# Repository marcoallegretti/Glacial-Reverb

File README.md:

# Koloured-Verb

A 12 HP Eurorack stereo reverb built on a Daisy Patch SM, using the
[eurorack-blocks](https://github.com/ohmtech-rdi/eurorack-blocks) framework.
Three boards: a carrier for the Daisy, a control board, and the panel.

Twelve reverb voices grouped into six families, ten post-reverb tail effects
grouped into five families, and a freeze pad with ducking.

## Rooms

Selected with the **ROOM** button. Short press cycles the family (RGB colour),
long press cycles the variant within it (RGB brightness dips = variant number).

| Family  | Colour  | Variants                          |
|---------|---------|-----------------------------------|
| Hall    | blue    | FDN tank · chamber                |
| Plate   | green   | Dattorro · vintage · dispersive   |
| Spring  | cyan    | classic · long tank · dispersive  |
| Shimmer | yellow  | octave up · octave down (Abyss)   |
| Cloud   | magenta | granular over an FDN tank         |
| Ambient | red     | modulated Hadamard FDN            |

Three variants per family is the ceiling: the LED renders a variant as a shade
of the family colour, and a fourth step is not readable against off.

The chamber runs a Moorer early-reflection tap bank and feeds the tank from the
taps rather than from the input, so each tap seeds the tank and the density
builds without the reflections reading as discrete echoes. The vintage plate
holds its high-frequency decay near a second whatever the decay knob does, as a
steel plate does. The long tank spreads its three spring delays while keeping
their chirp cutoffs together — the inverse of the short tank — and scatters at
the mid-point coupling ring. The dispersive voices use stretched-allpass chains
for the chirp.

## Tail effects

Selected with the **FX** button, same gesture (short = family, long = variant).
The red LED blinks the family number; None leaves the LED off. Each effect is
added over the untouched tail, so amount 0 is a true bypass.

| Family   | Variants                       |
|----------|--------------------------------|
| None     | —                              |
| Pitch    | octave up · sub · chord (5th)  |
| Modulate | chorus · formant               |
| Texture  | granular · reverse             |
| Resonant | resonator · droplet            |

## Panel

| Control   | Function                                                        |
|-----------|-----------------------------------------------------------------|
| FX pot    | Morph: model character and tail-effect depth together           |
| DECAY     | Tail length                                                     |
| MIX       | Wet added over the dry (additive, not a crossfade)              |
| PRE DL    | Pre-delay                                                       |
| DUCK      | Input ducks the reverb                                          |
| FRZ LV    | Frozen pad level                                                |
| FRZ MX    | How much new signal enters the frozen pad                       |
| FRZ btn   | Short press = freeze on/off · long press = tank-only on/off     |
| ROOM btn  | Short = room family · long = variant                            |
| FX btn    | Short = effect family · long = variant                          |
| FRZ G     | Gate: forces freeze on                                          |
| FX / FRZ LV / MIX / DECAY | CV over the corresponding pot                   |
| IN L/R    | Audio in (R normalled to L)                                     |
| OUT L/R   | Audio out                                                       |

CV drives continuous character; the buttons handle discrete structure. Room and
effect selection step discretely rather than sweeping: a switch renders both
voices through a 150 ms crossfade and clears the outgoing one only once it is
silent, so the tail carries across a switch.

## Layout

```
eurorack/
  KoloredVerb.erbui          panel and control definition
  KoloredVerb.{h,cpp}        UI glue: selectors, gestures, LEDs
  KoloredVerbDsp.{h,cpp}     freeze pad, duck, mix, pre-delay wrapper
  dsp/                       reverb models, tail effects, shared DSP

hardware/
  core-board/                carrier: Daisy Patch SM, power, I/O expansion
  control-board/             pots, jacks, buttons, LEDs
  panel-board/               12 HP front panel
```

Each board folder holds its KiCad sources and a `fab/` directory with the
gerber zip and loose gerber set. See [hardware/README.md](hardware/README.md)
for the stack and what mates to what.

## Building

See [BUILD.md](BUILD.md) for the toolchain, firmware, simulator and board
fabrication. The `eurorack-blocks` framework is not vendored in this repository.

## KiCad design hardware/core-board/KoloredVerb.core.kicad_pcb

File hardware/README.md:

# Koloured-Verb — hardware

Three boards, one 12 HP module.

```
  panel-board      12 HP FR4 panel: cutouts and baked labels
       │  pots / jacks / LEDs poke through
  control-board    panel parts on F.Cu, carrier headers on B.Cu
       │  ZZ1-5 / ZZ7 / ZZ12 + J6 / J9 / J11 plug down into…
  core-board       Daisy Patch SM host, power, I/O expansion
       │  4× 5×2 sockets host…
  Daisy Patch SM   Electrosmith submodule (bought, not fabricated)
```

| Folder | Board | Size | Assembly |
|---|---|---|---|
| [`core-board/`](core-board/) | carrier | 59.75 × 109.65 mm | 45 SMD by JLCPCB, 12 through-hole by hand |
| [`control-board/`](control-board/) | pots, jacks, buttons, LEDs | 59.75 × 109.65 mm | all by hand; one SMD RGB LED |
| [`panel-board/`](panel-board/) | 12 HP panel | 60.75 × 128.65 mm | none |

All three are 2-layer, 1.6 mm FR4. Each folder holds its KiCad sources, a
`<board>.bom.csv`, and `fab/` with the gerber zip and the loose set it was built
from. The core board also carries `fab/*-jlcpcb-bom.csv` and `-cpl.csv` for
assembly.

`ZZ10` on the control board is **DNP** — the core board carries no microSD, so
that header has no mating socket.

## Gerbers

```sh
kicad-cli pcb export gerbers --no-protel-ext \
  --layers F.Cu,B.Cu,F.Mask,B.Mask,F.Paste,B.Paste,F.Silkscreen,B.Silkscreen,Edge.Cuts \
  -o <board>/fab/gerber/ <board>/<name>.kicad_pcb
kicad-cli pcb export drill -o <board>/fab/gerber/ <board>/<name>.kicad_pcb
```

then zipped from `fab/gerber/`. The panel yields no paste layers — it carries no
SMD pads.

## Regenerating

The panel comes from `eurorack/KoloredVerb.erbui`; its labels are baked vector
outlines and cannot be edited in KiCad:

```sh
python3 hardware/panel-board/regen_panel.py
```

The control board cannot be regenerated — `erbb build hardware` parses it with a
KiCad-6-era reader that throws on KiCad 10 net syntax. Edit it in KiCad and treat
the committed board as the source of truth.

The core board's assembly files are derived from its own PCB:

```sh
"…/KiCad/10.0/bin/python.exe" hardware/core-board/derive_assembly.py
```

## Licensing

The control board and panel are generated from eurorack-blocks blocks, and the
core board derives from its kivu12. All carry **CC BY-SA 4.0** by derivation.
See [THIRD-PARTY.md](../THIRD-PARTY.md).

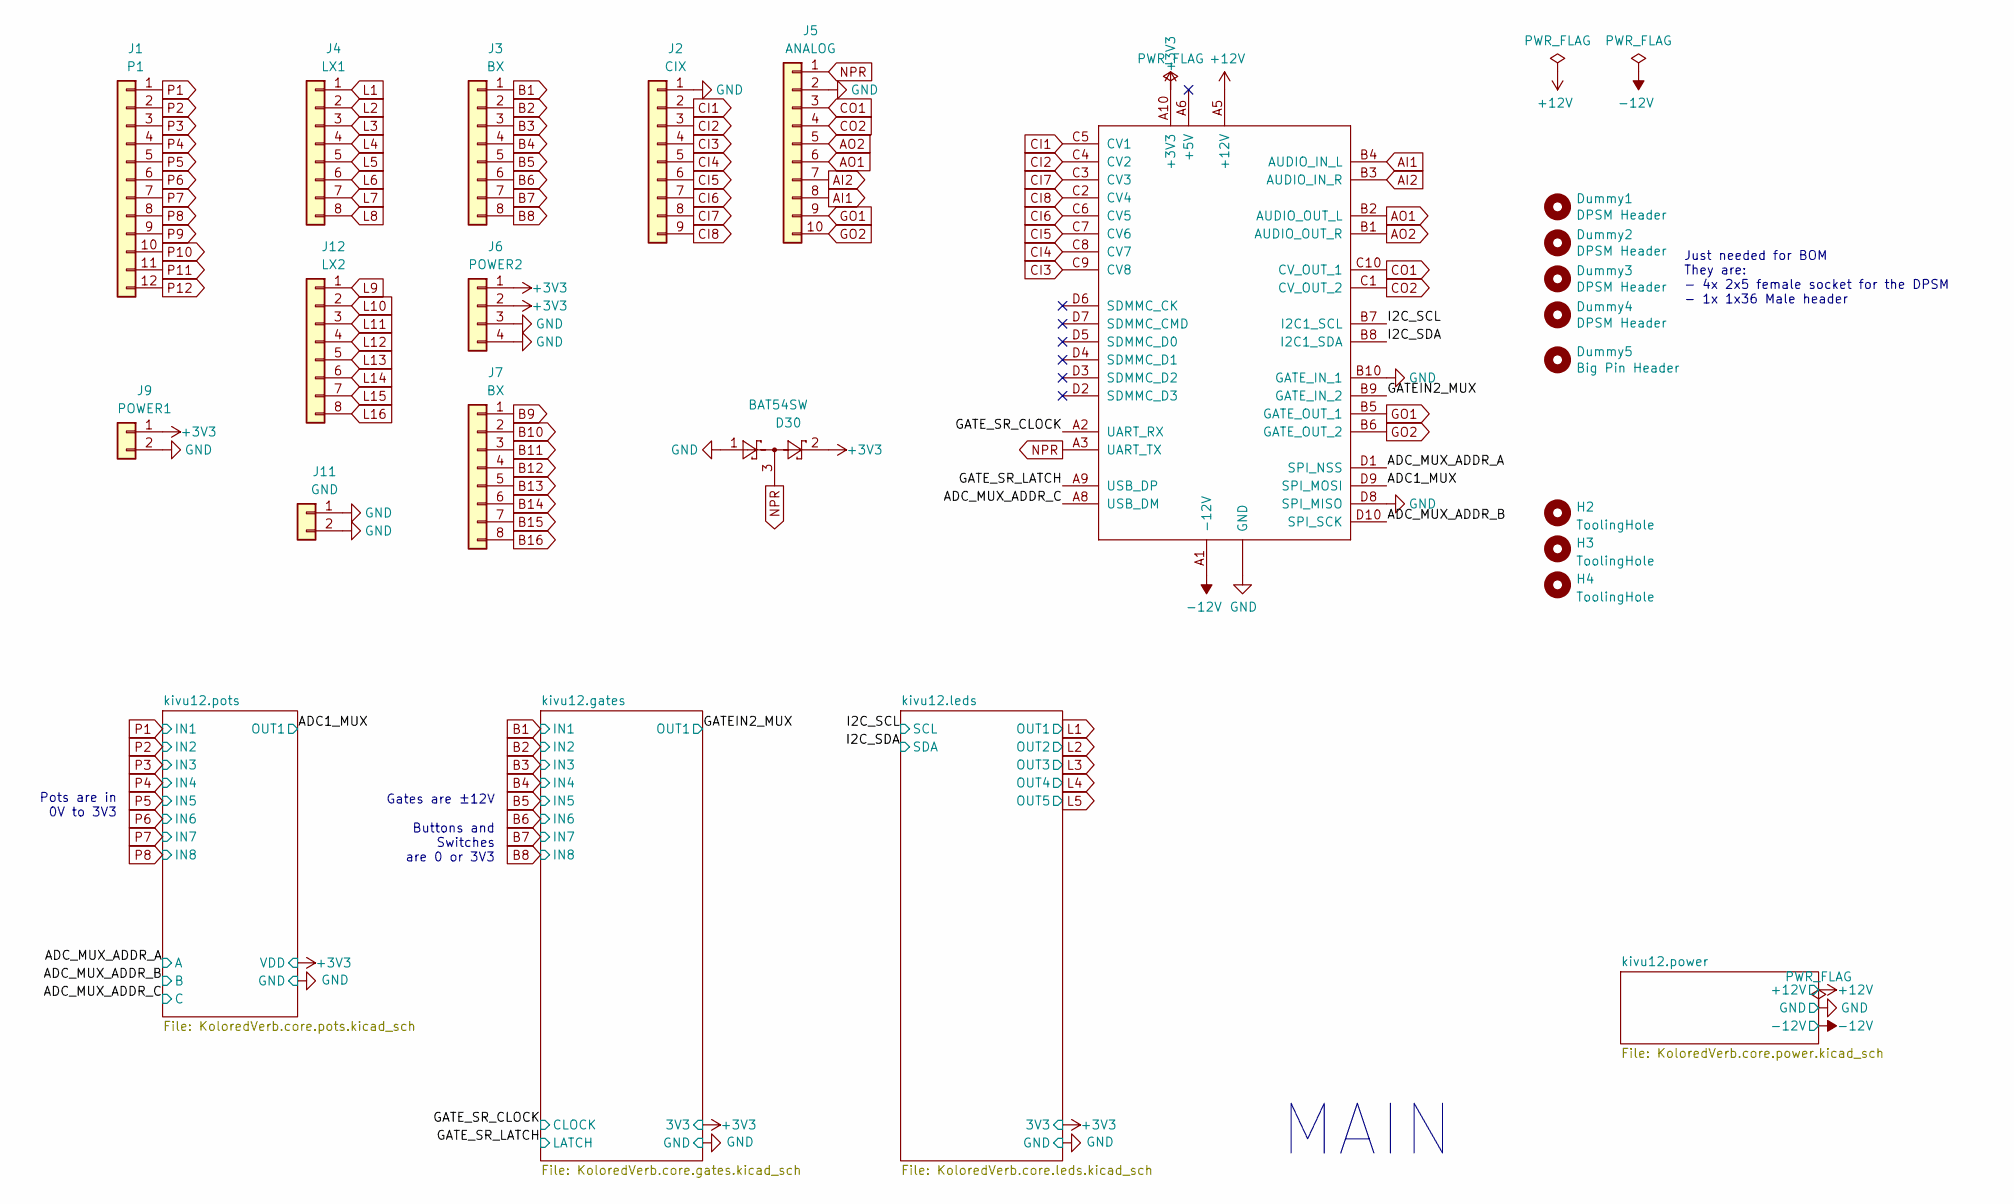
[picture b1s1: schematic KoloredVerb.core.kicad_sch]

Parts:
D30: BAT54SW; SOT-323_SC-70; MPN BAT54SW; JlcPcbPartNumber C22466373
DPSM1: DaisyPatchSm_Rev1; DaisyPatchSm; MPN DAISY-PATCH-SM
Dummy1, Dummy2, Dummy3, Dummy4: DPSM Header; Empty; MPN PPPC052LFBN-RC
Dummy5: Big Pin Header; Empty; MPN PBC36SAAN
H2, H3, H4: ToolingHole; JlcPcbToolingHole
J1: P1; PinSocket_1x12_P2.54mm_Vertical; MPN PPTC121LFBN-RC
J2: CIX; PinSocket_1x09_P2.54mm_Vertical; MPN PPTC091LFBN-RC
J3, J7: BX; PinSocket_1x08_P2.54mm_Vertical; MPN PPTC081LFBN-RC
J4: LX1; PinSocket_1x08_P2.54mm_Vertical; MPN PPTC081LFBN-RC
J5: ANALOG; PinSocket_1x10_P2.54mm_Vertical; MPN PPTC101LFBN-RC
J6: POWER2; PinSocket_1x04_P2.54mm_Vertical; MPN PPTC041LFBN-RC
J9: POWER1; PinSocket_1x02_P2.54mm_Vertical; MPN PPTC021LFBN-RC
J11: GND; PinSocket_1x02_P2.54mm_Vertical; MPN PPTC021LFBN-RC
J12: LX2; PinSocket_1x08_P2.54mm_Vertical; MPN PPTC081LFBN-RC

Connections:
+3V3: D30.2, DPSM1.A10 (+3V3), J6.1, J6.2, J9.1; also elsewhere on the board
+12V: DPSM1.A5 (+12V); also elsewhere on the board
-12V: DPSM1.A1 (-12V); also elsewhere on the board
/ADC1_MUX: DPSM1.D9 (SPI_MOSI); also elsewhere on the board
/ADC_MUX_ADDR_A: DPSM1.D1 (SPI_NSS); also elsewhere on the board
/ADC_MUX_ADDR_B: DPSM1.D10 (SPI_SCK); also elsewhere on the board
/ADC_MUX_ADDR_C: DPSM1.A8 (USB_DM); also elsewhere on the board
/GATEIN2_MUX: DPSM1.B9 (GATE_IN_2); also elsewhere on the board
/GATE_SR_CLOCK: DPSM1.A2 (UART_RX); also elsewhere on the board
/GATE_SR_LATCH: DPSM1.A9 (USB_DP); also elsewhere on the board
/I2C_SCL: DPSM1.B7 (I2C1_SCL); also elsewhere on the board
/I2C_SDA: DPSM1.B8 (I2C1_SDA); also elsewhere on the board
AI1: DPSM1.B4 (AUDIO_IN_L), J5.8
AI2: DPSM1.B3 (AUDIO_IN_R), J5.7
AO1: DPSM1.B2 (AUDIO_OUT_L), J5.6
AO2: DPSM1.B1 (AUDIO_OUT_R), J5.5
B1: J3.1; also elsewhere on the board
B2: J3.2; also elsewhere on the board
B3: J3.3; also elsewhere on the board
B4: J3.4; also elsewhere on the board
B5: J3.5; also elsewhere on the board
B6: J3.6; also elsewhere on the board
B7: J3.7; also elsewhere on the board
B8: J3.8; also elsewhere on the board
B9: J7.1
B10: J7.2
B11: J7.3
B12: J7.4
B13: J7.5
B14: J7.6
B15: J7.7
B16: J7.8
CI1: DPSM1.C5 (CV1), J2.2
CI2: DPSM1.C4 (CV2), J2.3
CI3: DPSM1.C9 (CV8), J2.4
CI4: DPSM1.C8 (CV7), J2.5
CI5: DPSM1.C7 (CV6), J2.6
CI6: DPSM1.C6 (CV5), J2.7
CI7: DPSM1.C3 (CV3), J2.8
CI8: DPSM1.C2 (CV4), J2.9
CO1: DPSM1.C10 (CV_OUT_1), J5.3
CO2: DPSM1.C1 (CV_OUT_2), J5.4
GND: D30.1, DPSM1.A4 (GND), DPSM1.A7 (GND), DPSM1.B10 (GATE_IN_1), DPSM1.D8 (SPI_MISO), J2.1, J5.2, J6.3, J6.4, J9.2, J11.1, J11.2; also elsewhere on the board
GO1: DPSM1.B5 (GATE_OUT_1), J5.9
GO2: DPSM1.B6 (GATE_OUT_2), J5.10
L1: J4.1; also elsewhere on the board
L2: J4.2; also elsewhere on the board
L3: J4.3; also elsewhere on the board
L4: J4.4; also elsewhere on the board
L5: J4.5; also elsewhere on the board
L6: J4.6
L7: J4.7
L8: J4.8
L9: J12.1
L10: J12.2
L11: J12.3
L12: J12.4
L13: J12.5
L14: J12.6
L15: J12.7
L16: J12.8
NPR: D30.3, DPSM1.A3 (UART_TX), J5.1
P1: J1.1; also elsewhere on the board
P2: J1.2; also elsewhere on the board
P3: J1.3; also elsewhere on the board
P4: J1.4; also elsewhere on the board
P5: J1.5; also elsewhere on the board
P6: J1.6; also elsewhere on the board
P7: J1.7; also elsewhere on the board
P8: J1.8; also elsewhere on the board
P9: J1.9
P10: J1.10
P11: J1.11
P12: J1.12

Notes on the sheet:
Just needed for BOM They are: - 4x 2x5 female socket for the DPSM - 1x 1x36 Male header
Pots are in 0V to 3V3
Gates are ±12V Buttons and Switches are 0 or 3V3
MAIN

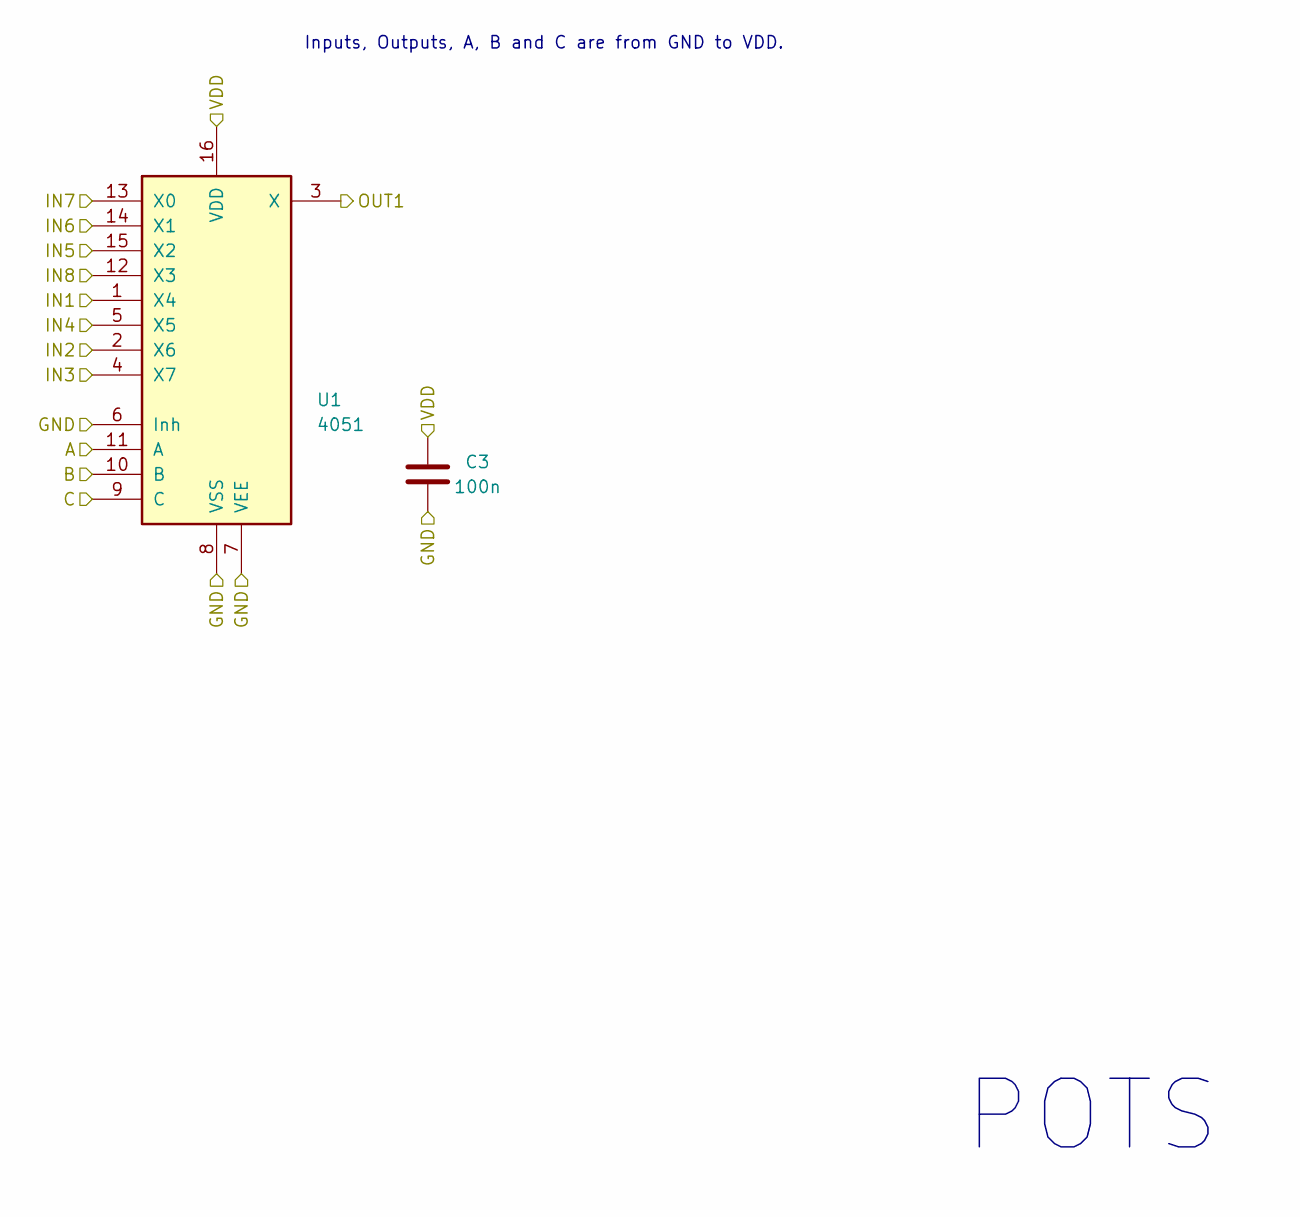
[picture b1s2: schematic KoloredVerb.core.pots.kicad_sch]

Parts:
C3: 100n; C_0603_1608Metric; MPN CC0603KRX7R9BB104; JlcPcbPartNumber C14663
U1: 4051; TSSOP-16_4.4x5mm_P0.65mm; MPN CD4051BPWR; JlcPcbPartNumber C54587

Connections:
+3V3: C3.2, U1.16 (VDD); also elsewhere on the board
/ADC1_MUX: U1.3 (X); also elsewhere on the board
/ADC_MUX_ADDR_A: U1.11 (A); also elsewhere on the board
/ADC_MUX_ADDR_B: U1.10 (B); also elsewhere on the board
/ADC_MUX_ADDR_C: U1.9 (C); also elsewhere on the board
GND: C3.1, U1.6 (Inh), U1.7 (VEE), U1.8 (VSS); also elsewhere on the board
P1: U1.1 (X4); also elsewhere on the board
P2: U1.2 (X6); also elsewhere on the board
P3: U1.4 (X7); also elsewhere on the board
P4: U1.5 (X5); also elsewhere on the board
P5: U1.15 (X2); also elsewhere on the board
P6: U1.14 (X1); also elsewhere on the board
P7: U1.13 (X0); also elsewhere on the board
P8: U1.12 (X3); also elsewhere on the board

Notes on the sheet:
Inputs, Outputs, A, B and C are from GND to VDD.
POTS

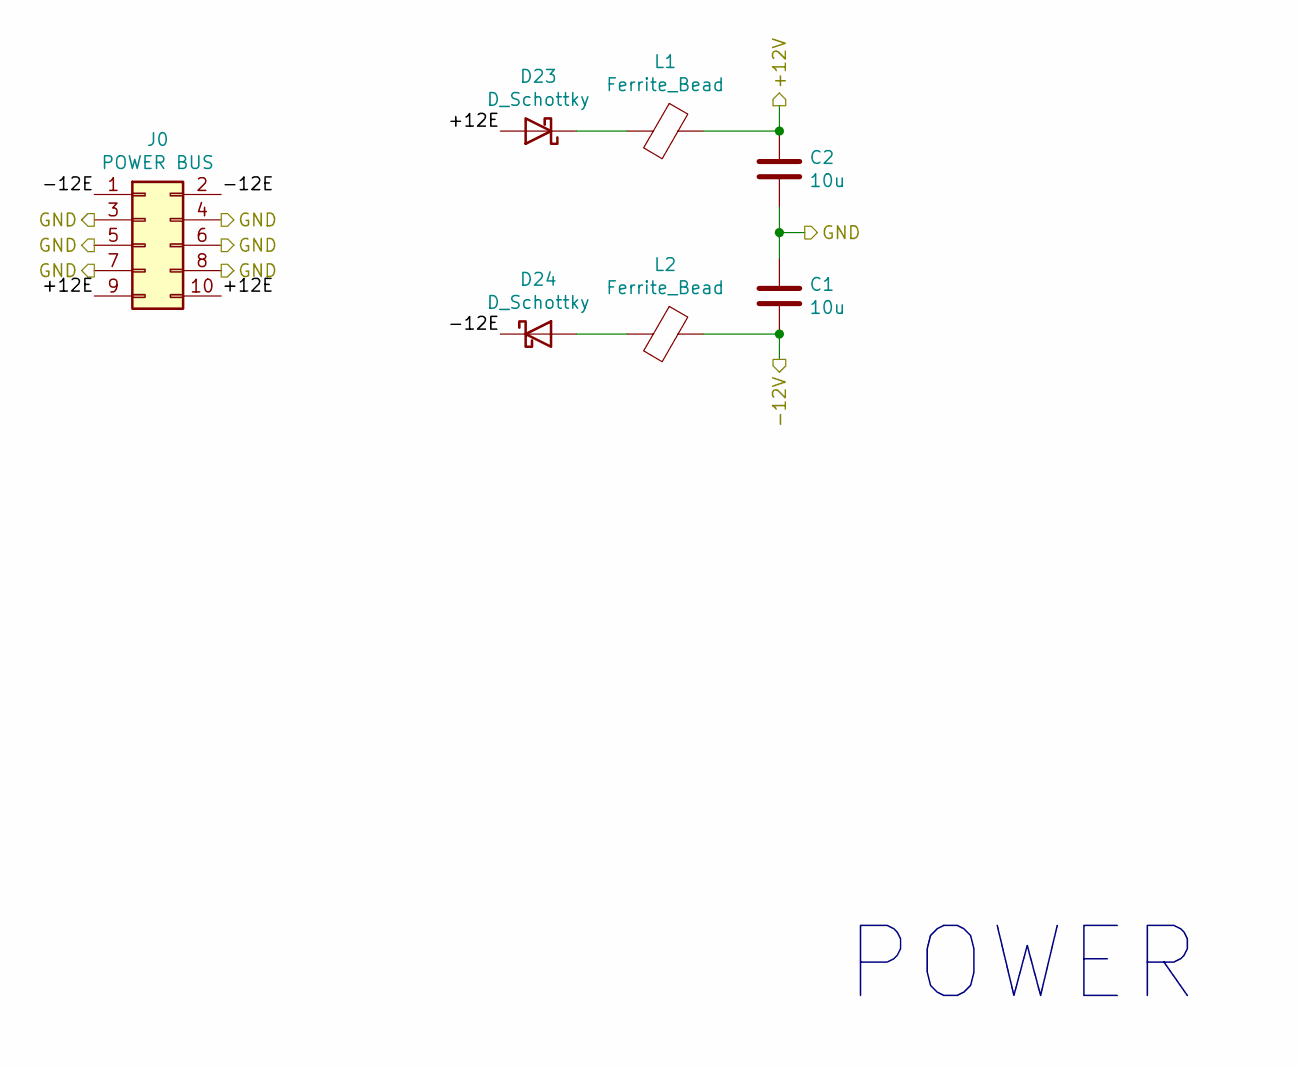
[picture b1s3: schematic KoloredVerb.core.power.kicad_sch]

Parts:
C1, C2: 10u; C_0805_2012Metric; MPN CL21A106KAYNNNE; JlcPcbPartNumber C15850
D23, D24: D_Schottky; D_SOD-123; MPN B5819W SL; JlcPcbPartNumber C8598
J0: POWER BUS; IDC-Header_2x05_P2.54mm_Vertical; MPN 61201021621
L1, L2: Ferrite_Bead; L_0603_1608Metric; MPN BLM18AG102SN1D; JlcPcbPartNumber C85824

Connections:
+12V: C2.1, L1.1; also elsewhere on the board
-12V: C1.2, L2.1; also elsewhere on the board
/kivu12.power/+12E: D23.2 (A), J0.9, J0.10
/kivu12.power/-12E: D24.1 (K), J0.1, J0.2
GND: C1.1, C2.2, J0.3, J0.4, J0.5, J0.6, J0.7, J0.8; also elsewhere on the board
unnamed: D23.1 (K), L1.2
unnamed: D24.2 (A), L2.2

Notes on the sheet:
POWER

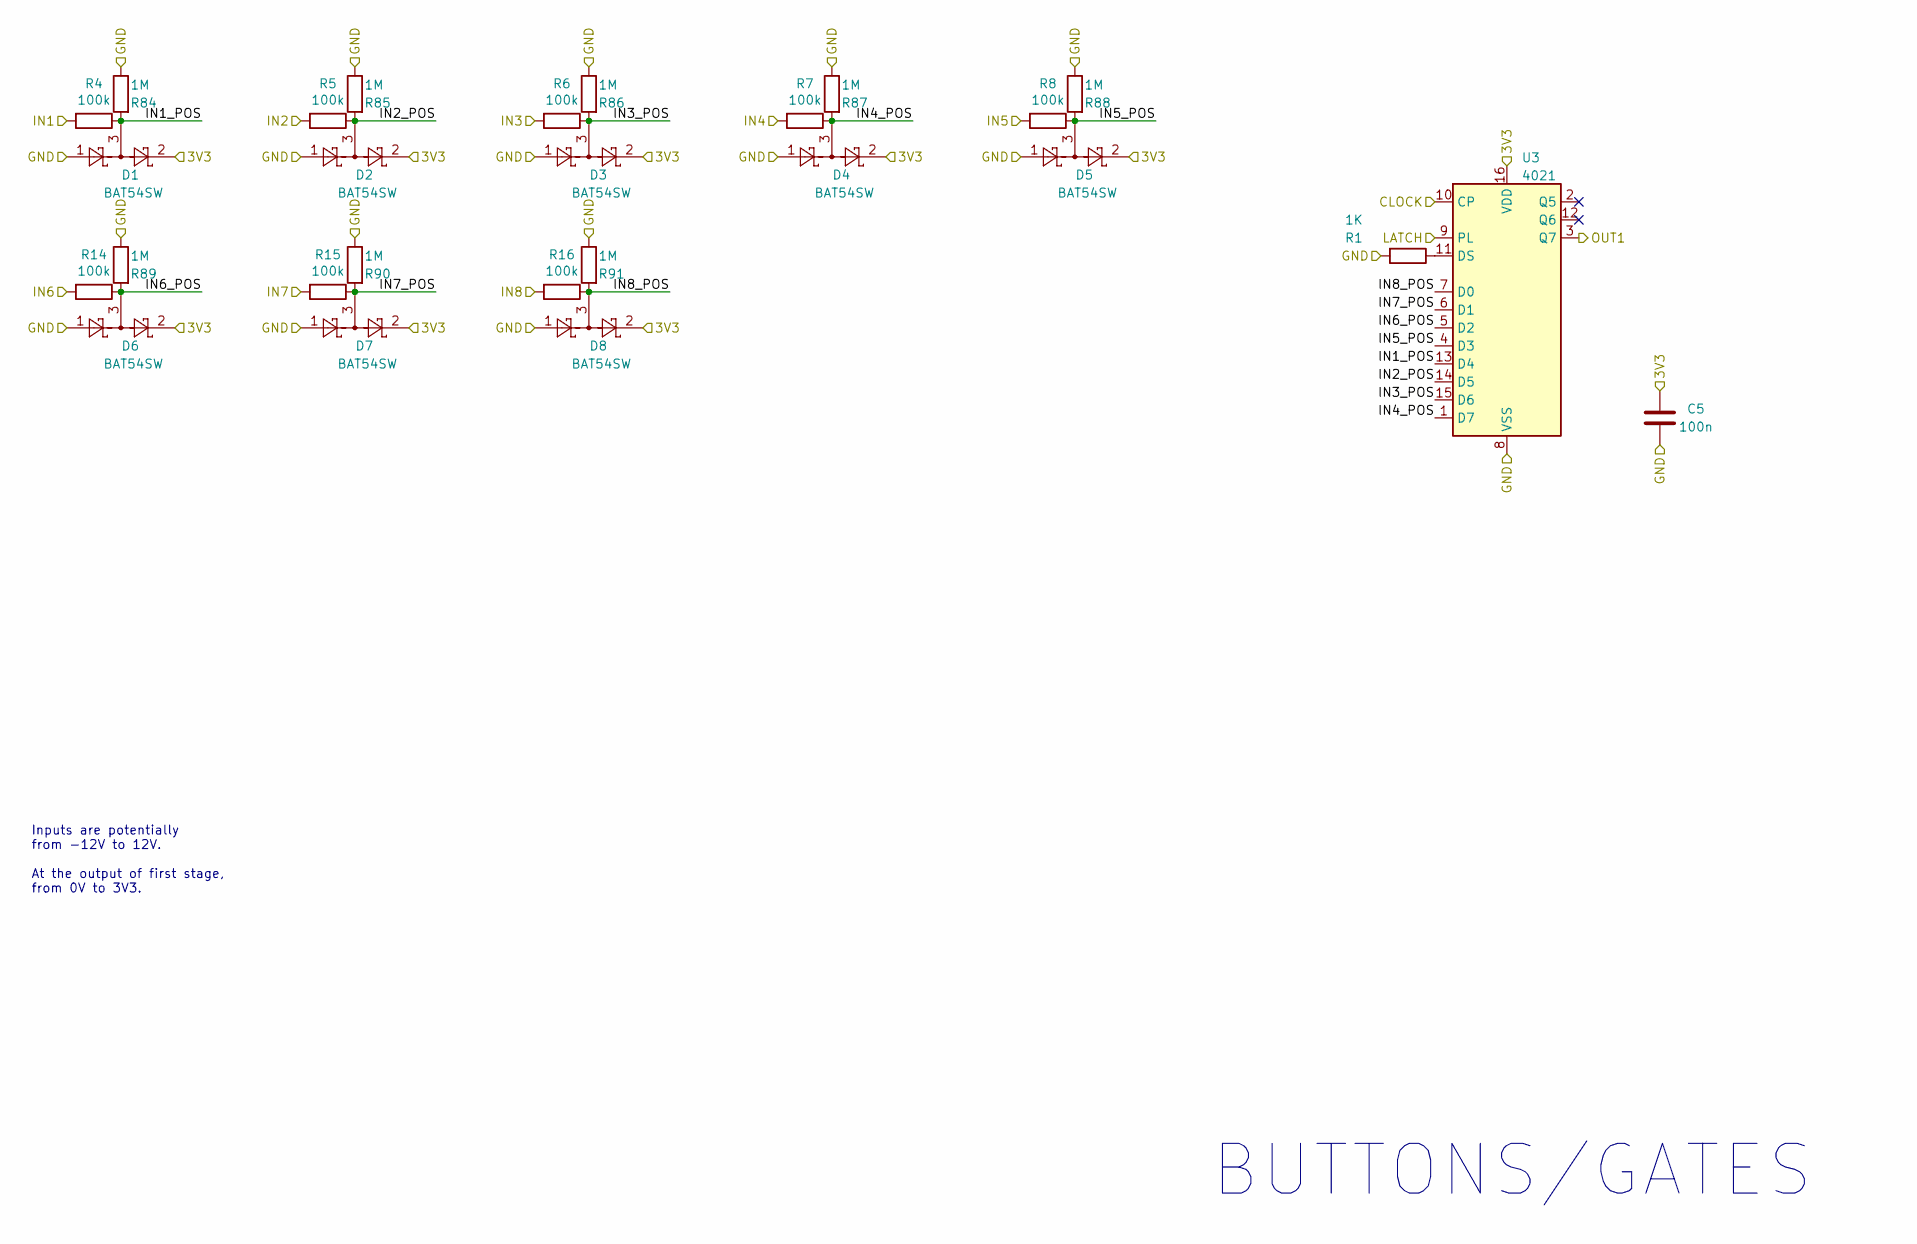
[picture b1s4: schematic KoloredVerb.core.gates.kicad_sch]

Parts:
C5: 100n; C_0603_1608Metric; MPN CC0603KRX7R9BB104; JlcPcbPartNumber C14663
D1, D2, D3, D4, D5, D6, D7, D8: BAT54SW; SOT-323_SC-70; MPN BAT54SW; JlcPcbPartNumber C22466373
R1: 1K; R_0603_1608Metric; MPN 0603WAF1001T5E; JlcPcbPartNumber C21190
R4, R5, R6, R7, R8, R14, R15, R16: 100k; R_0603_1608Metric; MPN 0603WAF1003T5E; JlcPcbPartNumber C25803
R84, R85, R86, R87, R88, R89, R90, R91: 1M; R_0603_1608Metric; MPN 0603WAF1004T5E; JlcPcbPartNumber C22935
U3: 4021; TSSOP-16_4.4x5mm_P0.65mm; MPN CD4021BPWR; JlcPcbPartNumber C2877061

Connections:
+3V3: C5.2, D1.2, D2.2, D3.2, D4.2, D5.2, D6.2, D7.2, D8.2, U3.16 (VDD); also elsewhere on the board
/GATEIN2_MUX: U3.3 (Q7); also elsewhere on the board
/GATE_SR_CLOCK: U3.10 (CP); also elsewhere on the board
/GATE_SR_LATCH: U3.9 (PL); also elsewhere on the board
/kivu12.gates/IN1_POS: D1.3, R4.1, R84.2, U3.13 (D4)
/kivu12.gates/IN2_POS: D2.3, R5.1, R85.2, U3.14 (D5)
/kivu12.gates/IN3_POS: D3.3, R6.1, R86.2, U3.15 (D6)
/kivu12.gates/IN4_POS: D4.3, R7.1, R87.2, U3.1 (D7)
/kivu12.gates/IN5_POS: D5.3, R8.1, R88.2, U3.4 (D3)
/kivu12.gates/IN6_POS: D6.3, R14.1, R89.2, U3.5 (D2)
/kivu12.gates/IN7_POS: D7.3, R15.1, R90.2, U3.6 (D1)
/kivu12.gates/IN8_POS: D8.3, R16.1, R91.2, U3.7 (D0)
B1: R4.2; also elsewhere on the board
B2: R5.2; also elsewhere on the board
B3: R6.2; also elsewhere on the board
B4: R7.2; also elsewhere on the board
B5: R8.2; also elsewhere on the board
B6: R14.2; also elsewhere on the board
B7: R15.2; also elsewhere on the board
B8: R16.2; also elsewhere on the board
GND: C5.1, D1.1, D2.1, D3.1, D4.1, D5.1, D6.1, D7.1, D8.1, R1.2, R84.1, R85.1, R86.1, R87.1, R88.1, R89.1, R90.1, R91.1, U3.8 (VSS); also elsewhere on the board
unnamed: R1.1, U3.11 (DS)

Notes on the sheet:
BUTTONS/GATES
Inputs are potentially from -12V to 12V. At the output of first stage, from 0V to 3V3.

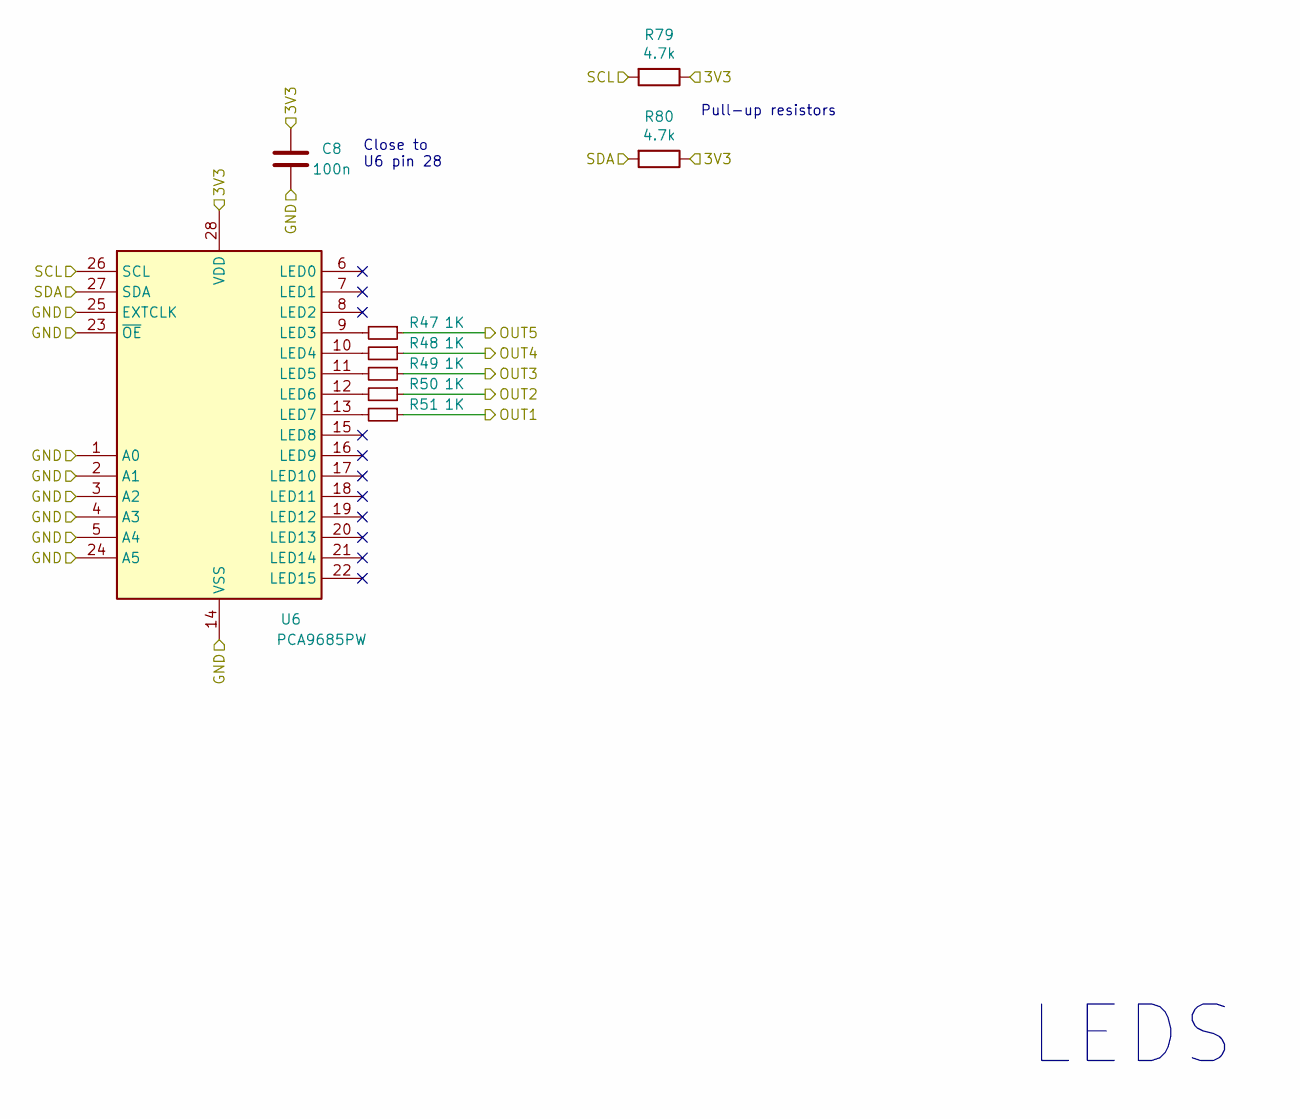
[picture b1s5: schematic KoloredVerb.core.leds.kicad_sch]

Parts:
C8: 100n; C_0603_1608Metric; MPN CC0603KRX7R9BB104; JlcPcbPartNumber C14663
R47, R48, R49, R50, R51: 1K; R_0603_1608Metric; MPN 0603WAF1001T5E; JlcPcbPartNumber C21190
R79, R80: 4.7k; R_0603_1608Metric; MPN 0603WAF4701T5E; JlcPcbPartNumber C23162
U6: PCA9685PW; TSSOP-28_4.4x9.7mm_P0.65mm; MPN PCA9685PW; JlcPcbPartNumber C2678753

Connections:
+3V3: C8.2, R79.1, R80.1, U6.28 (VDD); also elsewhere on the board
/I2C_SCL: R79.2, U6.26 (SCL); also elsewhere on the board
/I2C_SDA: R80.2, U6.27 (SDA); also elsewhere on the board
GND: C8.1, U6.1 (A0), U6.2 (A1), U6.3 (A2), U6.4 (A3), U6.5 (A4), U6.14 (VSS), U6.23 (~OE), U6.24 (A5), U6.25 (EXTCLK); also elsewhere on the board
L1: R51.1; also elsewhere on the board
L2: R50.1; also elsewhere on the board
L3: R49.1; also elsewhere on the board
L4: R48.1; also elsewhere on the board
L5: R47.1; also elsewhere on the board
unnamed: R47.2, U6.9 (LED3)
unnamed: R48.2, U6.10 (LED4)
unnamed: R49.2, U6.11 (LED5)
unnamed: R50.2, U6.12 (LED6)
unnamed: R51.2, U6.13 (LED7)

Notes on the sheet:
Close to U6 pin 28
Pull-up resistors
LEDS

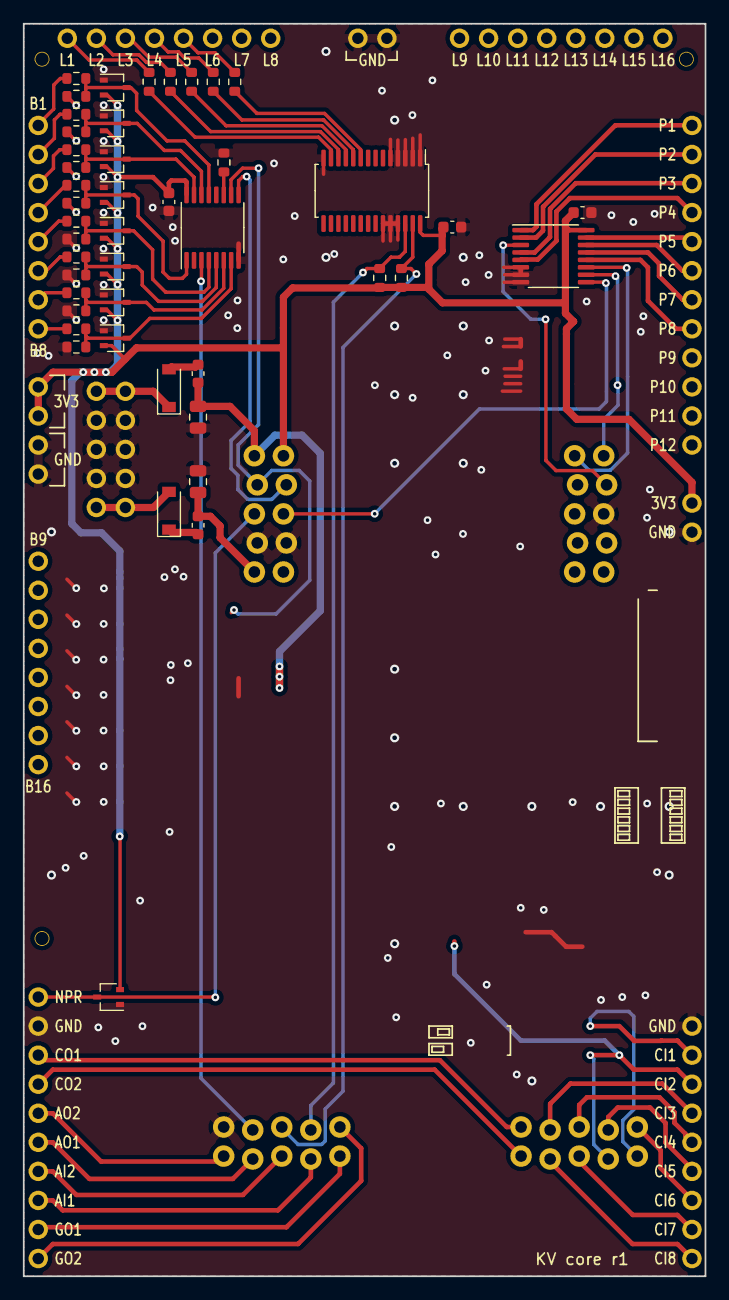
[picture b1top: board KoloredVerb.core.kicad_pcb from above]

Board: 2 copper layers, 59.6 x 109.5 mm, 65 parts (1 on the bottom side), 69 nets.

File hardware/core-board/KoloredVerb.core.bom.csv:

References;Description;MPN;Quantity;Distributor;Distributor Part Number;LCSC Part Number
C1 C2;CAP CER 10UF 25V X5R 0805;CL21A106KAYNNNE;2;Digikey;1276-2891-1-ND;C15850
C3 C5 C8;CAP CER 0.1UF 25V X7R 0603;CC0603KRX7R9BB104;3;Digikey;478-7018-1-ND;C14663
D1 D2 D3 D4 D5 D6 D7 D8 D30;DIODE ARRAY SCHOTTKY 40V SOT323;BAT54SW;9;Digikey;497-14153-1-ND;C22466373
D23 D24;DIODE SCHOTTKY 40V 1A SOD123;B5819W SL;2;Digikey;1N5819HW-FDICT-ND;C8598
Dummy1 Dummy2 Dummy3 Dummy4;CONN HDR 10POS 0.1 GOLD PCB;PPPC052LFBN-RC;4;Digikey;S7108-ND;
Dummy5;CONN HEADER VERT 36POS 2.54MM;PBC36SAAN;1;Digikey;S1011E-36-ND;
J0;CONN HEADER VERT 10POS 2.54MM;61201021621;1;Digikey;732-2094-ND;
J1;CONN HDR 12POS 0.1 TIN PCB;PPTC121LFBN-RC;1;Digikey;S6100-ND;
J2;CONN HDR 9POS 0.1 TIN PCB;PPTC091LFBN-RC;1;Digikey;S7007-ND;
J3 J7;CONN HDR 8POS 0.1 TIN PCB;PPTC081LFBN-RC;2;Digikey;S7006-ND;
J4;CONN HDR 8POS 0.1 TIN PCB;PPTC081LFBN-RC;1;Digikey;S7006-ND;
J5;CONN HDR 10POS 0.1 TIN PCB;PPTC101LFBN-RC;1;Digikey;S7008-ND;
J6;CONN HDR 4POS 0.1 TIN PCB;PPTC041LFBN-RC;1;Digikey;S7002-ND;
J9;CONN HDR 2POS 0.1 TIN PCB;PPTC021LFBN-RC;1;Digikey;S7000-ND;
J11;CONN HDR 2POS 0.1 TIN PCB;PPTC021LFBN-RC;1;Digikey;S7000-ND;
J12;CONN HDR 8POS 0.1 TIN PCB;PPTC081LFBN-RC;1;Digikey;S7006-ND;
L1 L2;FERRITE BEAD 1 KOHM 0603 1LN;BLM18AG102SN1D;2;Digikey;732-1586-1-ND;C85824
R1 R47 R48 R49 R50 R51;RES SMD 1K OHM 1% 1/10W 0603;0603WAF1001T5E;6;Digikey;311-1KLDCT-ND;C21190
R4 R5 R6 R7 R8 R14 R15 R16;RES SMD 100K OHM 1% 1/10W 0603;0603WAF1003T5E;8;Digikey;541-100KHCT-ND;C25803
R79 R80;RES SMD 4.7K OHM 1% 1/10W 0603;0603WAF4701T5E;2;Digikey;311-4.70KHRCT-ND;C23162
R84 R85 R86 R87 R88 R89 R90 R91;RES SMD 1M OHM 1% 1/10W 0603;0603WAF1004T5E;8;Digikey;541-1.00MHCT-ND;C22935
U1;IC MUX/DEMUX 8X1 16TSSOP;CD4051BPWR;1;Digikey;296-11993-1-ND;C54587
U3;IC STATIC SHFT REG 8STG 16-TSSOP;CD4021BPWR;1;Digikey;296-14256-1-ND;C2877061
U6;IC LED DRIVER RGBA 28-TSSOP;PCA9685PW;1;Digikey;568-11925-1-ND;C2678753
DPSM1;Audio submodule, plugs into the 4 sockets below;DAISY-PATCH-SM;1;Electrosmith;DAISY-PATCH-SM;

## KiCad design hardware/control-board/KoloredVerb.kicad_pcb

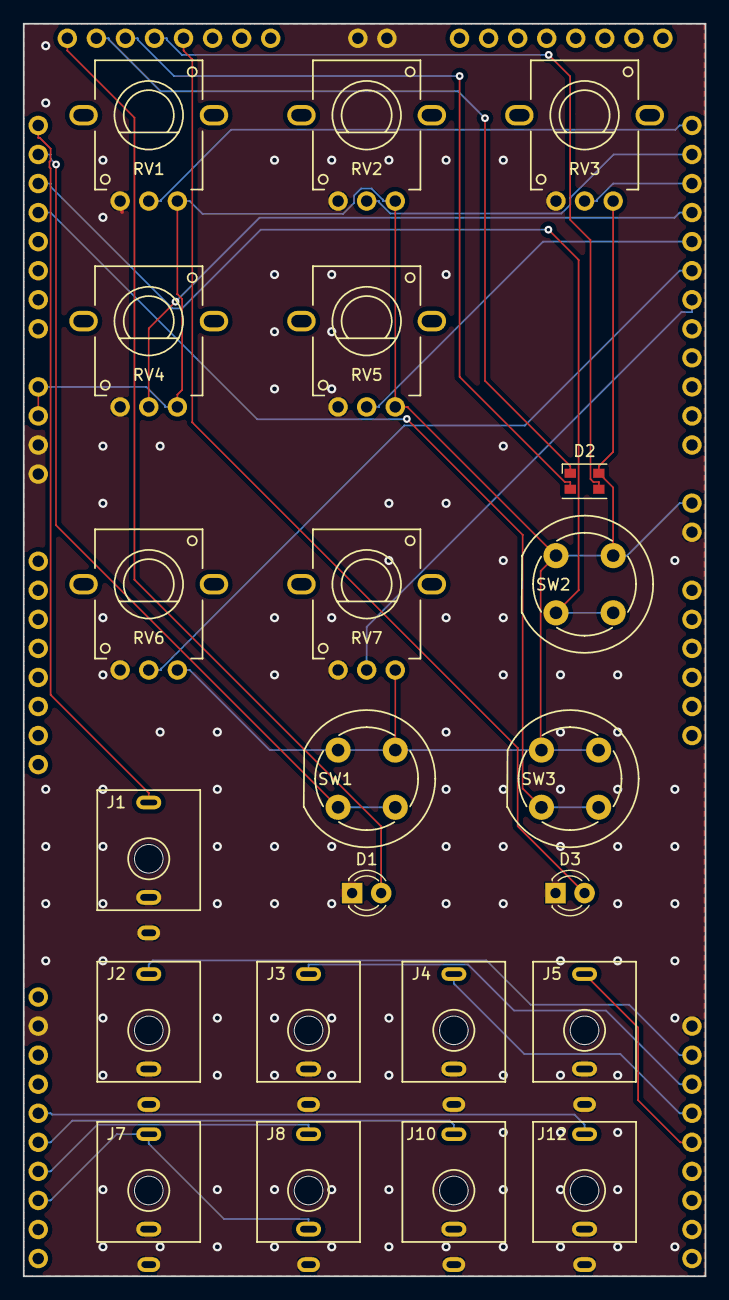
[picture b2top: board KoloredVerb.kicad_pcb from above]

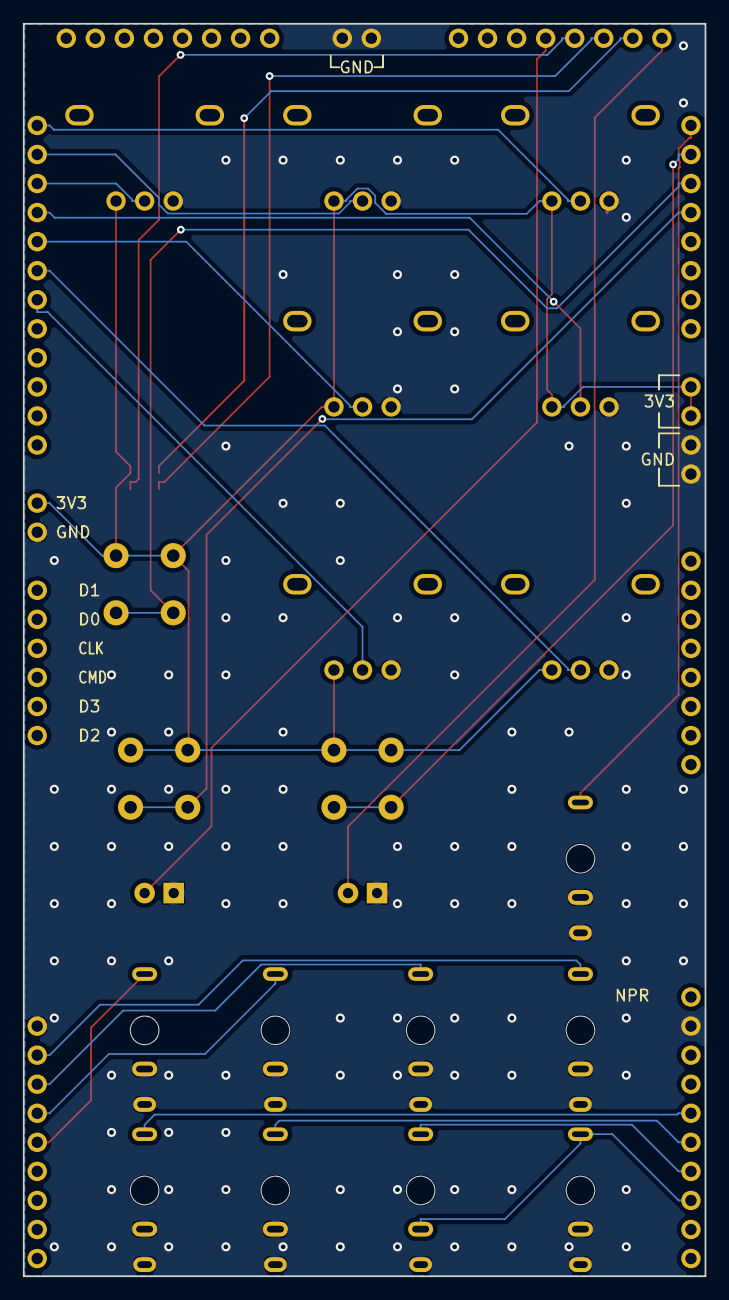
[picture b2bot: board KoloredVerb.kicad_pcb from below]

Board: 2 copper layers, 59.6 x 109.5 mm, 51 parts (11 on the bottom side), 26 nets.

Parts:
D1, D3: LED; LED_D3.0mm
D2: LED_RGBA; LED_Cree-PLCC4_3.2x2.8mm_CCW
H1: Header1; Empty
H2: Header2; Empty
H3, H4, H5, H6, H7, H8, H9: ROGAN 1PS; Empty
H10, H11, H12, H13, H14, H15, H16, H17, H18: KNURLED NUT; Empty
J1, J2, J3, J4, J5, J7, J8, J10, J12: IN; ThonkiconnJack
J6: POWER2; PinHeader_1x04_P2.54mm_Vertical
J9: POWER1; PinHeader_1x02_P2.54mm_Vertical
J11: GND; PinHeader_1x02_P2.54mm_Vertical
RV1, RV2, RV3, RV4, RV5, RV6, RV7: 100k; AlphaPot9ShaftD
SW1, SW2, SW3: SW_Push_Dual; SW_SPST_CKD6R
ZZ1: PX; PinHeader_1x12_P2.54mm_Vertical
ZZ2: CIX; PinHeader_1x09_P2.54mm_Vertical
ZZ3, ZZ7: BX; PinHeader_1x08_P2.54mm_Vertical
ZZ4, ZZ12: LX; PinHeader_1x08_P2.54mm_Vertical
ZZ5: ANALOG; PinHeader_1x10_P2.54mm_Vertical
ZZ10: SD; PinHeader_1x06_P2.54mm_Vertical

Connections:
+3V3: D2.4, J6.1, J6.2, J9.1, RV1.3, RV2.3, RV3.3, RV4.3, RV5.3, RV6.3, RV7.3, SW1.1, SW2.1, SW3.1
AI1: J7.T, J8.TN, ZZ5.8
AI2: J8.T, ZZ5.7
AO1: J10.T, ZZ5.6
AO2: J12.T, ZZ5.5
B1: J1.T, ZZ3.1
B2: SW1.2, ZZ3.2
B3: SW2.2, ZZ3.3
B4: SW3.2, ZZ3.4
CI1: J2.T, ZZ2.2
CI2: J3.T, ZZ2.3
CI3: J4.T, ZZ2.4
CI4: J5.T, ZZ2.5
GND: D1.1, D3.1, J1.S, J1.TN, J2.S, J2.TN, J3.S, J3.TN, J4.S, J4.TN, J5.S, J5.TN, J6.3, J6.4, J7.S, J7.TN, J8.S, J9.2, J10.S, J10.TN, J11.1, J11.2, J12.S, J12.TN, RV1.1, RV2.1, RV3.1, RV4.1, RV5.1, RV6.1, RV7.1, ZZ2.1, ZZ5.2
L1: D1.2, ZZ4.1
L2: D2.1, ZZ4.2
L3: D2.2, ZZ4.3
L4: D2.3, ZZ4.4
L5: D3.2, ZZ4.5
P1: RV1.2, ZZ1.1
P2: RV2.2, ZZ1.2
P3: RV3.2, ZZ1.3
P4: RV4.2, ZZ1.4
P5: RV5.2, ZZ1.5
P6: RV6.2, ZZ1.6
P7: RV7.2, ZZ1.7

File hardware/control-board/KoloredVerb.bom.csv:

References;Description;Remarks;Quantity;Distributor;Distributor Part Number;Distributor Part URL
ZZ1;CONN HEADER VERT 12POS 2.54MM;;1;Digikey;S1011E-12-ND;https://www.digikey.de/en/products/detail/sullins-connector-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
ZZ3, ZZ4, ZZ7, ZZ12;CONN HEADER VERT 8POS 2.54MM;;4;Digikey;S1011E-08-ND;https://www.digikey.de/en/products/detail/sullins-connector-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
J11, J9;CONN HEADER VERT 2POS 2.54MM;;2;Digikey;S1011E-02-ND;https://www.digikey.de/en/products/detail/sullins-connector-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
J6;CONN HEADER VERT 4POS 2.54MM;;1;Digikey;S1011E-04-ND;https://www.digikey.de/en/products/detail/sullins-connector-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
ZZ10;CONN HEADER VERT 6POS 2.54MM;DNP - the core board has no microSD, so this header has no mating socket. Fitting it leaves 6 pins in the gap above the core board.;0;Digikey;S1011E-06-ND;https://www.digikey.de/en/products/detail/sullins-connector-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
ZZ2;CONN HEADER VERT 9POS 2.54MM;;1;Digikey;S1011E-09-ND;https://www.digikey.de/en/products/detail/sullins-connector-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
ZZ5;CONN HEADER VERT 10POS 2.54MM;;1;Digikey;PBC10SAAN;https://www.digikey.de/en/products/detail/sullins-connector-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
RV1, RV2, RV3, RV4, RV5, RV6, RV7;ALPHA 9MM POTS – VERTICAL D-SHAFT;;7;Thonk;RD901F-B100K;https://www.thonk.co.uk/shop/alpha-9mm-pots-dshaft/
H3, H4, H5, H6, H7, H8, H9;1PS - Small Pointer (D Shaft) - Rogan PT Plastic Knob;;7;Thonk;;https://www.thonk.co.uk/shop/make-noise-mutable-style-knobs/
J1, J10, J12, J2, J3, J4, J5, J7, J8;Thonkiconn – 3.5mm Jack Sockets;;9;Thonk;PJ398SM;https://www.thonk.co.uk/shop/thonkiconn/
H10, H11, H12, H13, H14, H15, H16, H17, H18;Knurled Nuts;One nut bag contains already 50 pieces;9;Thonk;;https://www.thonk.co.uk/shop/thonkiconn/
SW1, SW2, SW3;C&K TACTILE SWITCH;Choose Black;3;Thonk;;https://www.thonk.co.uk/shop/radio-music-switch/
D1, D3;LED RED DIFFUSED T-1 T/H;;2;Digikey;754-1606-ND;https://www.digikey.com/en/products/detail/kingbright/WP710A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
D2;LED RGB SMD PLCC4 - Cree CLV1A-FKB (common anode, FX indicator);;1;Digikey;CLV1A-FKB-CJ1M1F1BB7R4S3;https://www.cree.com/led-components/media/documents/CLV1AFKB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
